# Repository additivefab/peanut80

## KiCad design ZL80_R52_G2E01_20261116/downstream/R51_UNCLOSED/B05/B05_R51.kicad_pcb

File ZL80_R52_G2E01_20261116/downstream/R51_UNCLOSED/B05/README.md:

# B05 R5.1 可编辑工程

打开 `B05_R51.kicad_pro`。根原理图组织 2 个子页；同名全局标签在本板工程内连接。

这是 R5 针脚网名/布局迁移，不是已闭合电路。4 个功能占位未定型：U1, C1, R1, U2。所有板均未布线；继承的 passive 针脚类型削弱 ERC 检查能力，需逐芯片核对。

3D STEP 是本体尺寸盒，不是厂商内部或完整连接器模型。板厚/器件高/正反面/插拔空间均须复核。

不得从此版本生成下单用 Gerber。原生打开、ERC、DRC、原理图-PCB一致性及人工签核尚未执行。

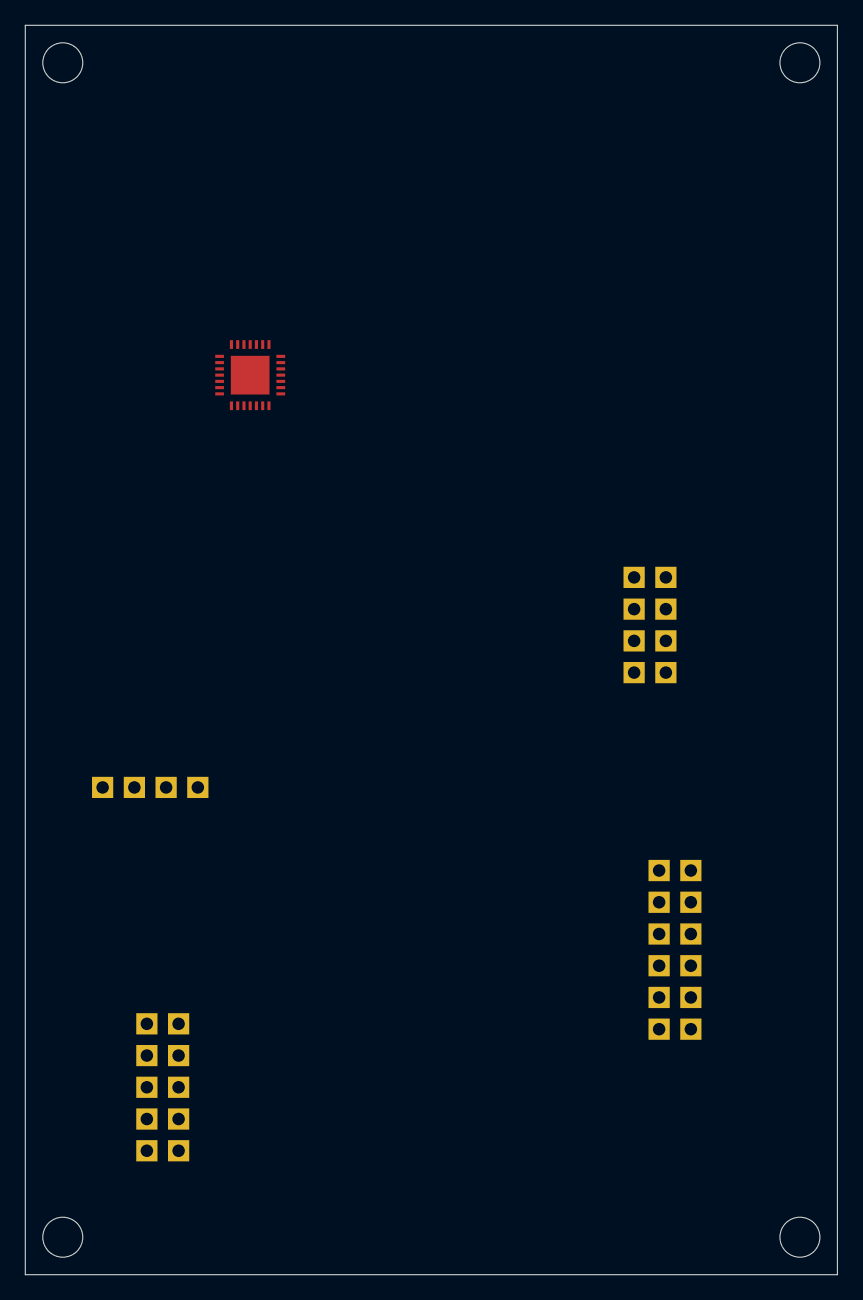
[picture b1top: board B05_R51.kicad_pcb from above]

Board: 4 copper layers, 65.0 x 100.0 mm, 12 parts (0 on the bottom side), 2 nets, no tracks yet.

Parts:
C1: VM_BULK_ZONE; B05_C1
J1: HEADER_1x4_P2.54; B05_J1
J2: HEADER_2x5_P2.54; B05_J2
J3: HEADER_2x6_P2.54; B05_J3
J4: HEADER_2x4_P2.54; B05_J4
MH1, MH2, MH3, MH4: NPTH; MountingHole_3.2
R1: SENSE_NETWORK_ZONE; B05_R1
U1: TMC2209_LA_PADS_PENDING; B05_U1
U2: ENC_LEVEL_BUFFER_ZONE; B05_U2

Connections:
5V: J2.1, J2.6, J4.8
GND: J2.2, J2.7, J3.11, J4.7

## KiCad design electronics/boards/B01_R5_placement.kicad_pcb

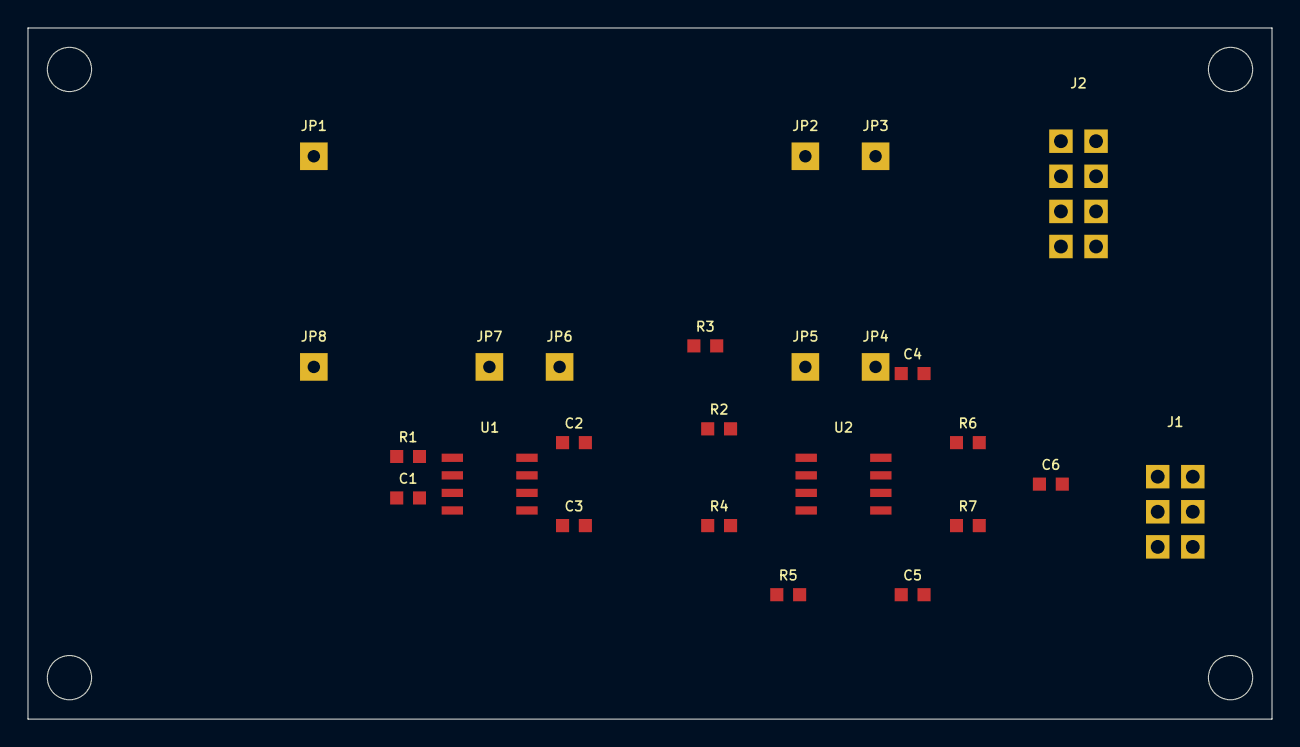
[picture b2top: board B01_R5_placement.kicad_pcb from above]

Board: 4 copper layers, 90.0 x 50.0 mm, 29 parts (0 on the bottom side), 16 nets, no tracks yet.

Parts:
C1: 1.5p_C0G; 0603
C2, C3, C4, C5: 100n; 0603
C6: 330p_DIFF_TRIAL; 0603
J1: HEADER_2x3_P2.54; header
J2: HEADER_2x4_P2.54; header
JP1, JP2, JP3, JP4, JP5, JP6, JP7, JP8: PMT_SOCKET_SINGLE; socket
MH1, MH2, MH3, MH4: NPTH
R1: 100k_0.1%; 0603
R2, R4: 499_0.1%; 0603
R3, R5: 1k_0.1%; 0603
R6, R7: 33R; 0603
U1: OPA828ID; soic8
U2: AD8138ARZ; soic8

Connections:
5VA_PMT: J2.4, JP4.1
+5VA: C2.1, C4.1, J2.1, U1.7, U2.3
-5VA: C3.1, C5.1, J2.3, U1.4, U2.6
ADC_A_N: C6.2, J1.3, R7.2
ADC_A_P: C6.1, J1.1, R6.2
ADC_VCM: J1.5, U2.2
AGND: C2.2, C3.2, C4.2, C5.2, J1.2, J1.4, J1.6, J2.2, J2.6, JP5.1, JP6.1, U1.3
D_A_N: R3.1, R7.1, U2.5
D_A_P: R5.1, R6.1, U2.4
FDA_N: R4.2, R5.2, U2.1
FDA_P: R2.2, R3.2, U2.8
OFFSET_0V5: J2.7, R4.1
PMT_I: C1.1, JP7.1, R1.1, U1.2
PMT_VCONT: J2.5, JP3.1
PMT_VREF: J2.8, JP2.1
TIA_OUT: C1.2, R1.2, R2.1, U1.6

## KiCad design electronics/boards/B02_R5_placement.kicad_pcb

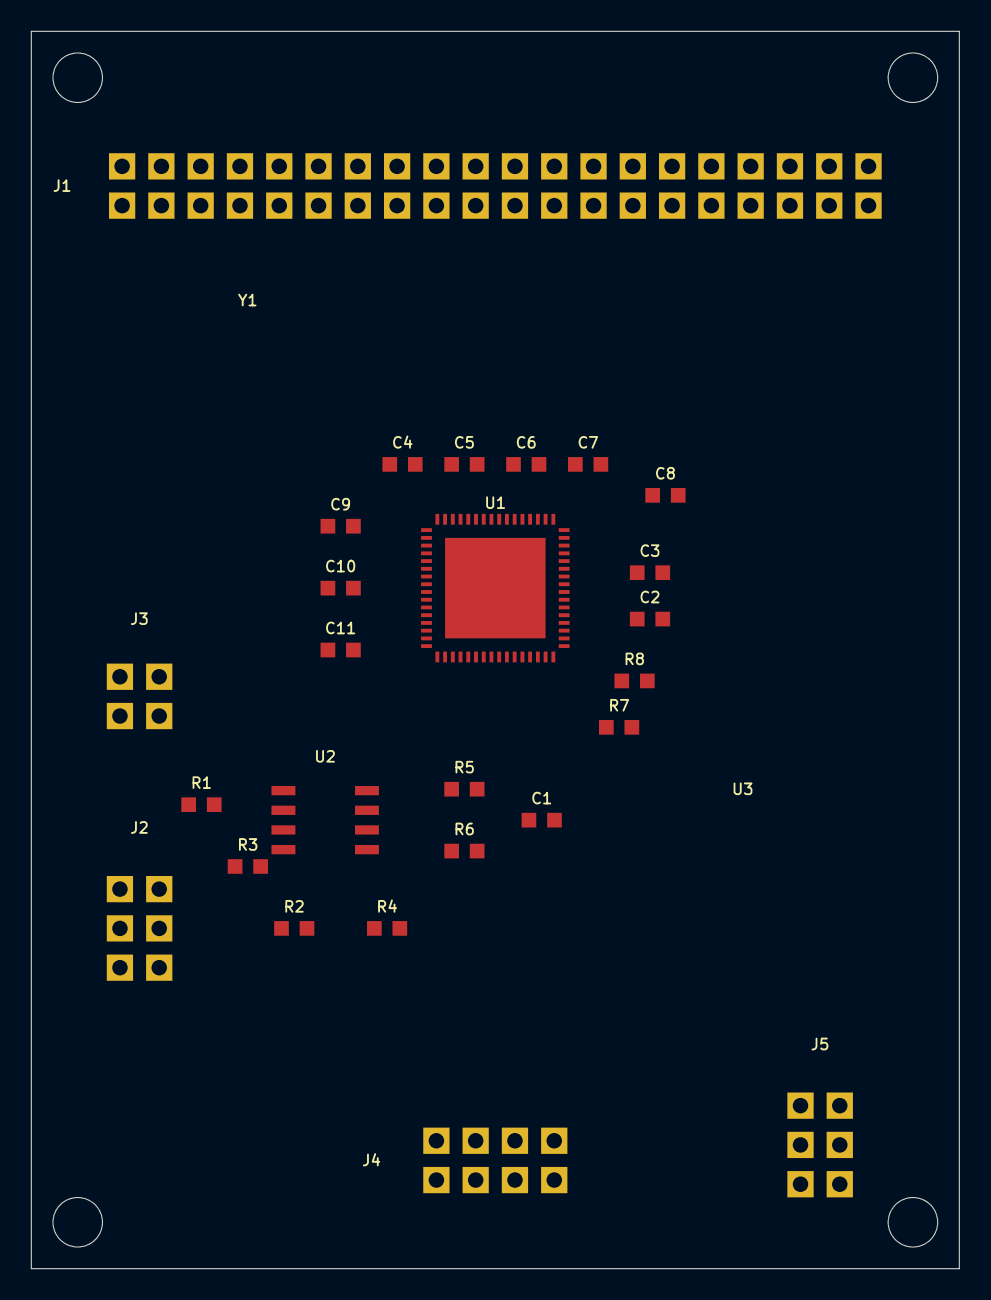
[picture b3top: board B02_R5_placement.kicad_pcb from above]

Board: 6 copper layers, 60.0 x 80.0 mm, 32 parts (0 on the bottom side), 52 nets, no tracks yet.

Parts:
C1: 330p_DIFF_TRIAL; 0603
C2: 1u; 0603
C3, C4, C5, C6, C7, C8, C9, C10, C11: 100n; 0603
J1: HEADER_2x20_P2.54; header
J2, J5: HEADER_2x3_P2.54; header
J3: HEADER_2x2_P2.54; header
J4: HEADER_2x4_P2.54; header
MH1, MH2, MH3, MH4: NPTH
R1, R2, R3, R4: 499; 0603
R5, R6: 33R; 0603
R7: 10k_1%; 0603
R8: 0R; 0603
U1: AD9268BCPZ-80; qfn64
U2: AD8138ARZ; soic8
U3: SPI_3V3_1V8_TRANSLATOR_RFQ; module
Y1: 20MHz_1V8_OSC_RFQ; module

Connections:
1V8A: C5.1, C7.1, C9.1, C11.1, J5.1, U1.49, U1.50, U1.53, U1.54, U1.59, U1.60, U1.63, U1.64
1V8D: C4.1, C6.1, C8.1, C10.1, J5.3, U1.10, U1.19, U1.28, U1.37
+5VA: J5.5, U2.3
-5VA: J5.6, U2.6
ADC_A_N: J2.3, U1.52
ADC_A_P: J2.1, U1.51
ADC_B_N: C1.2, R6.2, U1.61
ADC_B_P: C1.1, R5.2, U1.62
ADC_RBIAS: R7.1, U1.58
ADC_SENSE: R8.1, U1.56
ADC_VCM: J2.5, U1.57, U2.2
ADC_VREF: C2.1, C3.1, U1.55
AGND: C2.2, C3.2, C4.2, C5.2, C6.2, C7.2, C8.2, C9.2, C10.2, C11.2, J1.35, J1.36, J2.2, J2.4, J2.6, J3.2, J3.4, J4.2, J5.2, J5.4, R3.1, R7.2, R8.2, U1.65
DA0: J1.1, U1.25
DA1: J1.2, U1.26
DA2: J1.3, U1.27
DA3: J1.4, U1.29
DA4: J1.5, U1.30
DA5: J1.6, U1.31
DA6: J1.7, U1.32
DA7: J1.8, U1.33
DA8: J1.9, U1.34
DA9: J1.10, U1.35
DA10: J1.11, U1.36
DA11: J1.12, U1.38
DA12: J1.14, U1.39
DA13: J1.15, U1.40
DA14: J1.16, U1.41
DA15: J1.18, U1.42
DB0: J1.19, U1.4
DB1: J1.20, U1.5
DB2: J1.21, U1.6
DB3: J1.22, U1.7
DB4: J1.23, U1.8
DB5: J1.24, U1.9
DB6: J1.25, U1.11
DB7: J1.26, U1.12
DB8: J1.27, U1.13
DB9: J1.28, U1.14
DB10: J1.29, U1.15
DB11: J1.30, U1.16
DB12: J1.31, U1.17
DB13: J1.32, U1.18
DB14: J1.33, U1.20
DB15: J1.34, U1.21
DCOA: J1.13, U1.24
DCOB: J1.17, U1.23
D_B_N: R2.1, R6.1, U2.5
D_B_P: R4.1, R5.1, U2.4
REF_FDA_N: R3.2, R4.2, U2.1
REF_FDA_P: R1.2, R2.2, U2.8
REF_V: J3.1, J3.3, R1.1
